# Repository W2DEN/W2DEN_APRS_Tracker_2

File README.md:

# W2DEN_APRS_Tracker_2
Tracker with a menu
This version will include a menu to allow users to change some of the 'default' data. A new version 'thread' was created so the original Tracker did not change. this will allow other development without the menu system included.
Who knows, where this is going!
UPDATE 8/5/15: For all practical purposes the software is complete. There will be some code refinements, the menu system is 'brute force' coding and needs some sophisitcation.
Documentaion will be brought up to speed on the N4SER.org site. 
NOTE: libraries included with the Arduino IDE and/or the Tensyduino IDE are NOT captured here. They will be documented as time allows.
73
Den

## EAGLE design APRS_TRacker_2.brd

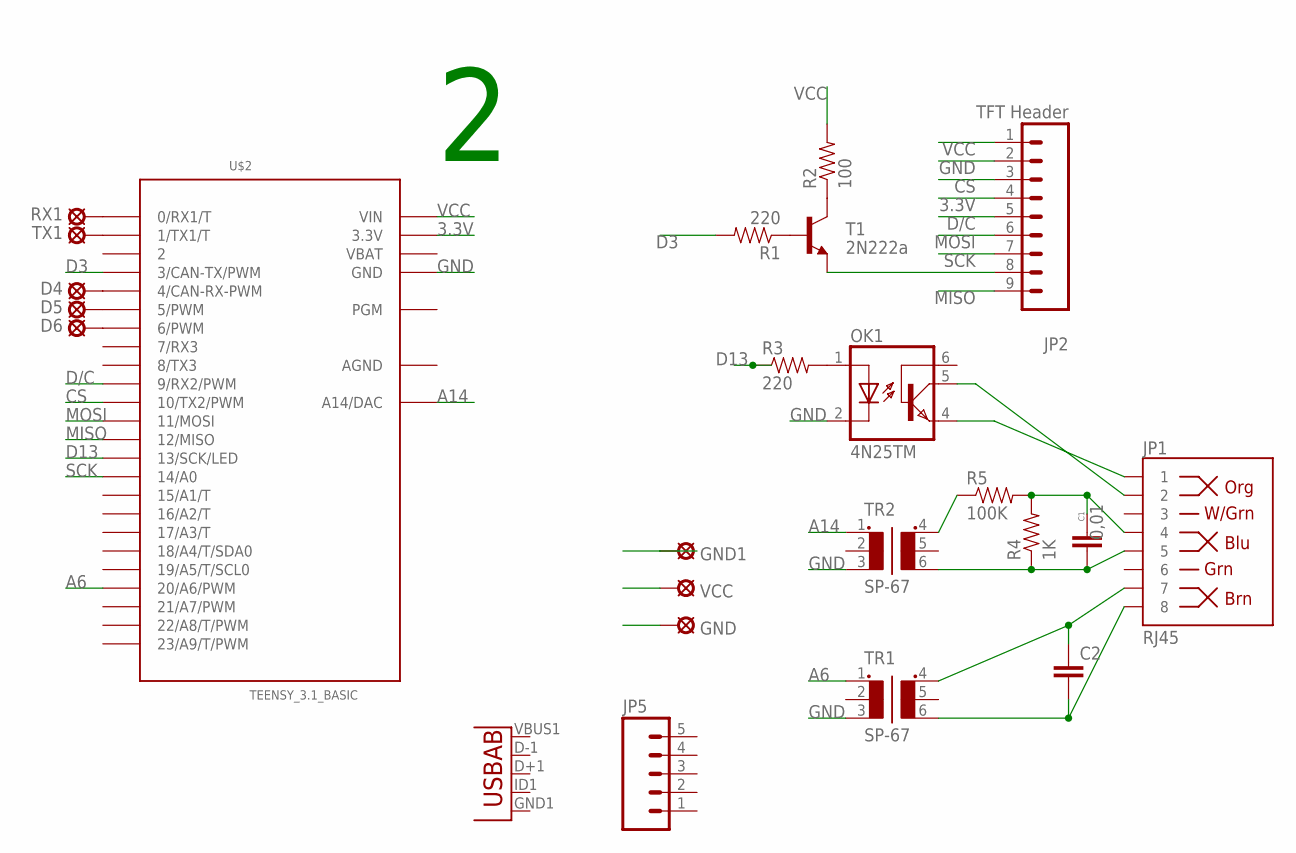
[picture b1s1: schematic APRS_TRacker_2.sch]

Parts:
C1: 0,01; CAP-PTH-SMALL2
C2: CAPPTH2; CAP-PTH-SMALL2
D4, D5, D6: LSP10
GND, GND1: LSP10
JP1: RJ45; RJ45-8
JP2: TFT Header; 1X09
JP5: M05PTH; 1X05
OK1: 4N25TM; DIL6-04
R1, R3: 220; AXIAL-0.4
R2: 100; AXIAL-0.4
R4: 1K; AXIAL-0.4
R5: 100K; AXIAL-0.4
RX1: LSP10
T1: 2N222a; TO-92
TR1, TR2: SP-67
TX1: LSP10
U$2: TEENSY_3.1_BASIC
U$4: USB-AB""; USB-AB-MICRO-SMD_V02_BOSS
VCC: LSP10

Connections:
3.3V: JP2.4, U$2.3.3V, U$2.3.3V1 (3.3V)
A6: TR1.1, U$2.20/A6 (20/A6/PWM)
A14: TR2.1, U$2.A14 (A14/DAC)
AGND: U$2.AGND
CS: JP2.3, U$2.10 (10/TX2/PWM)
D3: R1.P$2 (2), U$2.3 (3/CAN-TX/PWM)
D13: R3.P$1 (1), U$2.13 (13/SCK/LED)
D/C: JP2.5, U$2.9 (9/RX2/PWM)
GND: GND.MP, GND1.MP, JP2.2, OK1.2 (C), TR1.3, TR2.3, U$2.GND, U$2.GND1 (GND)
MISO: JP2.9, U$2.12 (12/MISO)
MOSI: JP2.6, U$2.11 (11/MOSI)
unnamed: R1.P$1 (1), T1.2 (B)
unnamed: R2.P$1 (1), T1.1 (C)
unnamed: OK1.1 (A), R3.P$2 (2)
unnamed: JP1.1, OK1.4 (EMI)
unnamed: JP1.2, OK1.5 (COL)
unnamed: C2.2, JP1.8, TR1.6
unnamed: C2.1, JP1.7, TR1.4
unnamed: C1.1, JP1.4, R4.P$2 (2), R5.P$2 (2)
unnamed: C1.2, JP1.5, R4.P$1 (1), TR2.6
unnamed: R5.P$1 (1), TR2.4
unnamed: D5.MP, U$2.5 (5/PWM)
unnamed: D6.MP, U$2.6 (6/PWM)
unnamed: D4.MP, U$2.4 (4/CAN-RX-PWM)
unnamed: RX1.MP, U$2.0 (0/RX1/T)
unnamed: TX1.MP, U$2.1 (1/TX1/T)
SCK: JP2.7, U$2.14/A0
T1: JP2.8, T1.3 (E)
VBAT: U$2.VBAT
VCC: JP2.1, R2.P$2 (2), U$2.VIN, VCC.MP

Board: 2 copper layers, 24 parts (1 on the bottom side), 28 nets, no tracks yet.

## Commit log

2015-07-06 :boom::camel: Added .gitattributes & .gitignore files
2015-07-06 Tracker with a menu
    Added the Push Button and Rotary Encoder code. Nothin in the menu yet.
2015-07-07 W2DEN Tracker 2 (with menu)
2015-07-16 Menu functional!!
    The menu system is now functional. RETURN, RETURN & SEND and UTC OFFSET
    are functioning. Good time to save this. Menu work will continue to
    include all user definable data under v 2.00.
2015-07-21 Lots of updates for the menu system
    Development continues on the menu. Auto DST removed as the menu can
    change the UTC offset. Menu functional for everything but the 3 text
    fields.
2015-07-29 Smart Beaconing Implements
    Smart Beaconing (TM) is now implemented. This may need some tweaking but
    it works. All SB parameters are stored in eePROM and user selectable via
    the SmartBeaconing sub-menu.
    Need to add constant time xmit delay override.
2015-07-30 Smart Beacon and Screen Update,
    Improvements to the stability of the Smart Beacon.
    Screen updated to clean it up and stop the flashing on update.
    The SB may need a % update as speed changes... this will be
    investigated.
2015-08-05 Menu complete
    The two level, 4 'page' menu is now complete. This allows user control
    of all APRS parameters. Well, any you'd want to change. The AX.25 page
    has not been fully tested due to a human induced hardware failure. next
    steps: update the software documentation on the N4SER.org site, code
    cleanup, and a smaller box.
    73 W2DEN
2015-08-05 Added some comments
2015-08-14 V 2.0 Software now complete
    W2DEN APRS Tracker 2.0 software development is complete. The AX.25
    comment field editor is fully functional. Any further development will
    released as new versions
2015-08-20 V2.01 complete
    Menu code updated, New single knob text editor improved. Screen On/Off
    menu option. This pretty much completes the code for the W2DEN Tracker.
2015-08-25 Version 2.02 debugged and ready
    Some debugging... fixed transmit time now working correctly. Added
    squelch detect (audio monitoring) to help avoid collisions.
2015-10-12 Display Rotate
    Rotated the display 180 degrees for the new box. Otherwise the code is
    stable and fully functional
2015-10-12 Eagle Tracker 2 Board
    This Eagle board is only airwires. Can be routed if you want to print
    it.
2016-05-05 Debug
    Corrected sub-menu rotation issues.
2016-07-10 DeBug Call sign error
    Thanks to Jan (VS6VOL) who has built a W2DEN Tracker for hi great input
    on debugging a call sign length bug.

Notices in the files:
parts and their libraries:
SparkFun-Connectors: Licensing: Creative Commons ShareAlike 4.0 International - https://creativecommons.org/licenses/by-sa/4.0
